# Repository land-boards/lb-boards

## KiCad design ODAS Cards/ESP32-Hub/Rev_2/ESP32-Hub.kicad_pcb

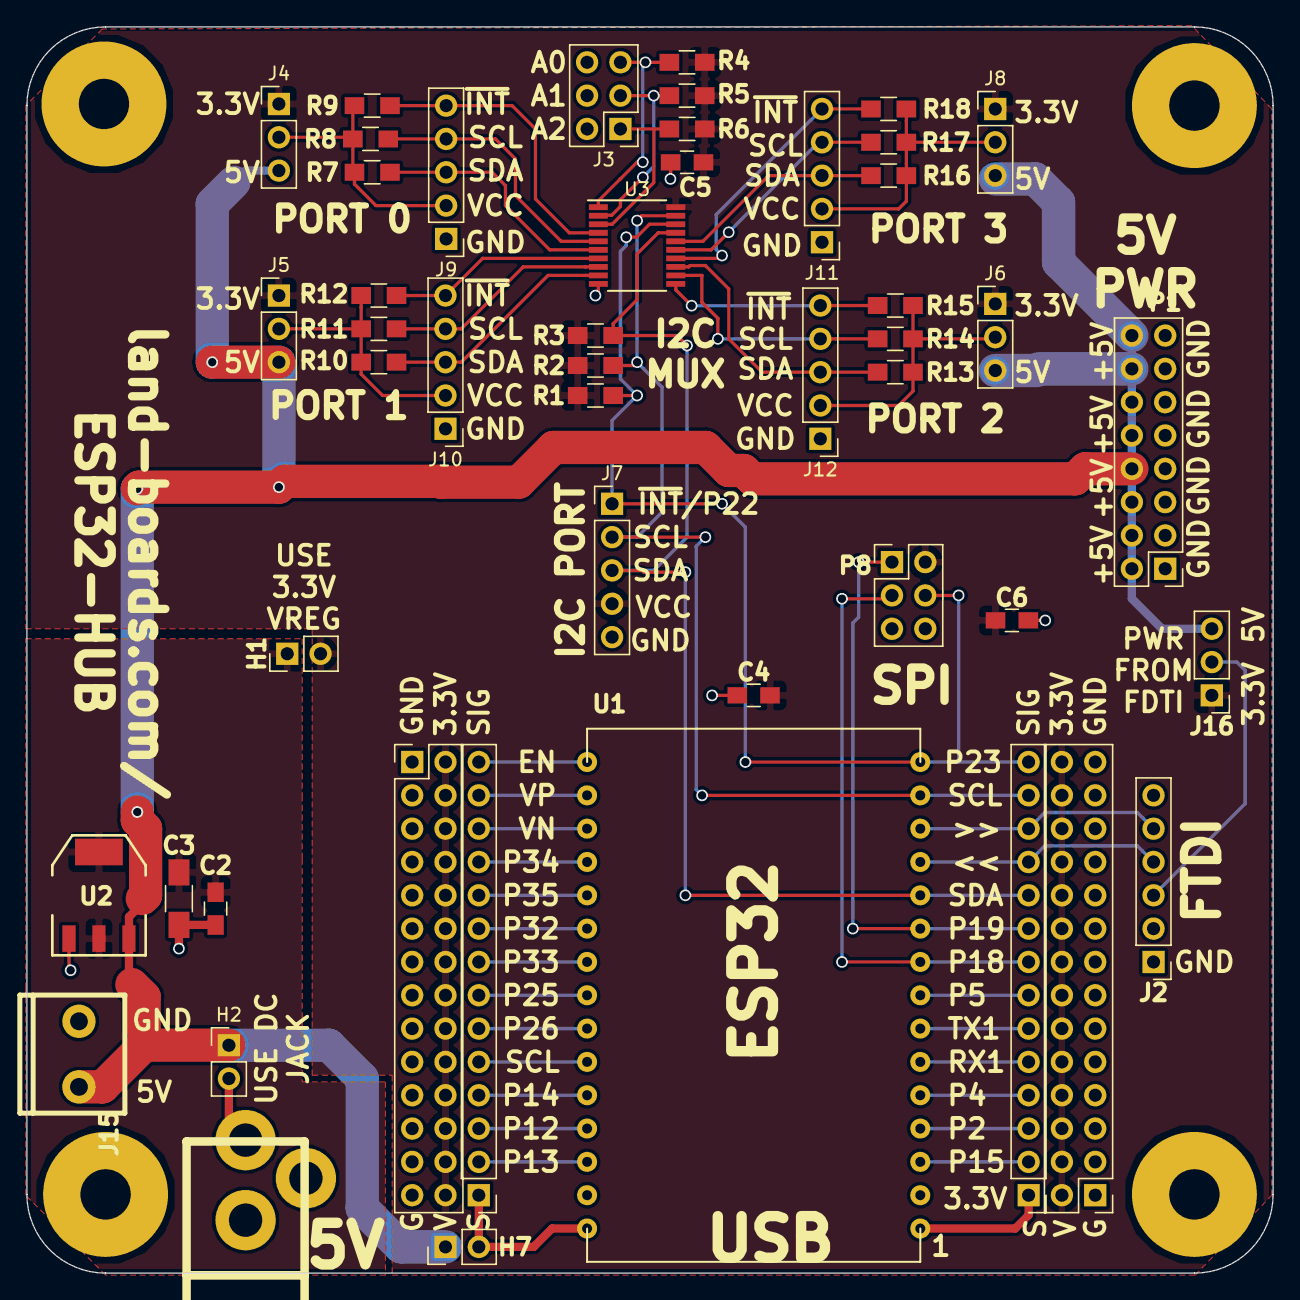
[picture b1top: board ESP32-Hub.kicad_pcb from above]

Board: 2 copper layers, 95.0 x 95.0 mm, 53 parts (0 on the bottom side), 53 nets.

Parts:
C2, C4, C5, C6: 0.1uF; C_0805_HandSoldering
C3: 10uF; C_1206_HandSoldering
H1, H2, H7: Conn_01x02; Pin_Header_Straight_1x02_Pitch2.54mm
J1: DCJ0202; DCJ-NEW
J2: FTDI; Pin_Header_Straight_1x06_Pitch2.54mm
J3: Conn_02x03_Odd_Even; Pin_Header_Straight_2x03_Pitch2.54mm
J4, J5, J6, J8, J16: Conn_01x03; Pin_Header_Straight_1x03_Pitch2.54mm
J7, J9, J10, J11, J12: Conn_01x05; Pin_Header_Straight_1x05_Pitch2.54mm
J15: Conn_01x02; TB2-5MM
MTG1, MTG2, MTG3: MTG_HOLE; MTG-6-32
MTG?1: MTG_HOLE; MTG-6-32
P1: Conn_02x08_Odd_Even; Pin_Header_Straight_2x08_Pitch2.54mm
P2, P11: Conn_02x14_Odd_Even; Pin_Header_Straight_2x14_Pitch2.54mm
P8: Conn_02x03_Odd_Even; Pin_Header_Straight_2x03_Pitch2.54mm
P12, P13: Conn_01x14; Pin_Header_Straight_1x14_Pitch2.54mm
R1, R4, R5, R6, R9, R12, R15, R18: 10K; R_0805_HandSoldering
R2, R3, R7, R8, R10, R11, R13, R14, R16, R17: 2.2K; R_0805_HandSoldering
U1: ESP32; ESP32_EXP
U2: AP1117; SOT223
U3: TCA9544A; TSSOP-20_4.4x6.5mm_Pitch0.65mm

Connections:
+3V3: C4.1, C5.1, C6.1, H1.2, J4.1, J5.1, J6.1, J7.4, J8.1, J16.1, P2.2, P2.4, P2.6, P2.8, P2.10, P2.12, P2.14, P2.16, P2.18, P2.20, P2.22, P2.24, P2.26, P2.28, P8.2, P11.2, P11.4, P11.6, P11.8, P11.10, P11.12, P11.14, P11.16, P11.18, P11.20, P11.22, P11.24, P11.26, P11.28, R1.1, R2.1, R3.1, R4.1, R5.1, R6.1, U3.20
+5V: H2.1, H7.1, J4.3, J5.3, J6.3, J8.3, J15.1, J16.3, P1.2, P1.4, P1.6, P1.8, P1.10, P1.12, P1.14, P1.16, U2.3
/A0: J3.5, R4.2, U3.1
/A1: J3.3, R5.2, U3.2
/A2: J3.1, R6.2, U3.3
/DCIN: H2.2, J1.1
/EN: P13.14, U1.16
/GP2: P12.3, U1.4
/GP4: P12.4, U1.5
/GP5: P12.7, U1.8
/GP12: P13.3, U1.27
/GP13: P13.2, U1.28
/GP14: P13.4, U1.26
/GP15: P12.2, U1.3
/GP18: P8.3, P12.8, U1.9
/GP19: P8.1, P12.9, U1.10
/GP23: J7.3, P8.4, P12.14, R3.2, U1.15, U3.17
/GP25: P13.7, U1.23
/GP26: P13.6, U1.24
/GP27: P13.5, U1.25
/GP32: P13.9, U1.21
/GP33: P13.8, U1.22
/GP34: P13.11, U1.19
/GP35: P13.10, U1.20
/INT0: J9.5, R9.2, U3.4
/INT1: J10.5, R12.2, U3.7
/INT2: J12.5, R15.2, U3.11
/INT3: J11.5, R18.2, U3.14
/RX0: J2.4, P12.11, U1.12
/RX1: P12.5, U1.6
/SC0: J9.4, R8.2, U3.5
/SC1: J10.4, R11.2, U3.8
/SC2: J12.4, R14.2, U3.12
/SC3: J11.4, R17.2, U3.15
/SD0: J9.3, R7.2, U3.6
/SD1: J10.3, R10.2, U3.9
/SD2: J12.3, R13.2, U3.13
/SD3: J11.3, R16.2, U3.16
/STM_SCL: J7.1, P12.13, R1.2, U1.14, U3.18
/STM_SDA: J7.2, P12.10, R2.2, U1.11, U3.19
/TX0: J2.5, P12.12, U1.13
/TX2: P12.6, U1.7
/VN: P13.12, U1.18
/VO3: C2.1, C3.1, H1.1, U2.2, U2.4
/VP: P13.13, U1.17
GND: C2.2, C3.2, C4.2, C5.2, C6.2, J1.2, J1.3, J2.1, J3.2, J3.4, J3.6, J7.5, J9.1, J10.1, J11.1, J12.1, J15.2, P1.1, P1.3, P1.5, P1.7, P1.9, P1.11, P1.13, P1.15, P2.1, P2.3, P2.5, P2.7, P2.9, P2.11, P2.13, P2.15, P2.17, P2.19, P2.21, P2.23, P2.25, P2.27, P8.6, P11.1, P11.3, P11.5, P11.7, P11.9, P11.11, P11.13, P11.15, P11.17, P11.19, P11.21, P11.23, P11.25, P11.27, U1.2, U1.29, U2.1, U3.10
unnamed: H7.2, P13.1, U1.30
unnamed: J4.2, J9.2, R7.1, R8.1, R9.1
unnamed: J5.2, J10.2, R10.1, R11.1, R12.1
unnamed: J8.2, J11.2, R16.1, R17.1, R18.1
unnamed: J6.2, J12.2, R13.1, R14.1, R15.1
unnamed: J2.3, J16.2
unnamed: P12.1, U1.1

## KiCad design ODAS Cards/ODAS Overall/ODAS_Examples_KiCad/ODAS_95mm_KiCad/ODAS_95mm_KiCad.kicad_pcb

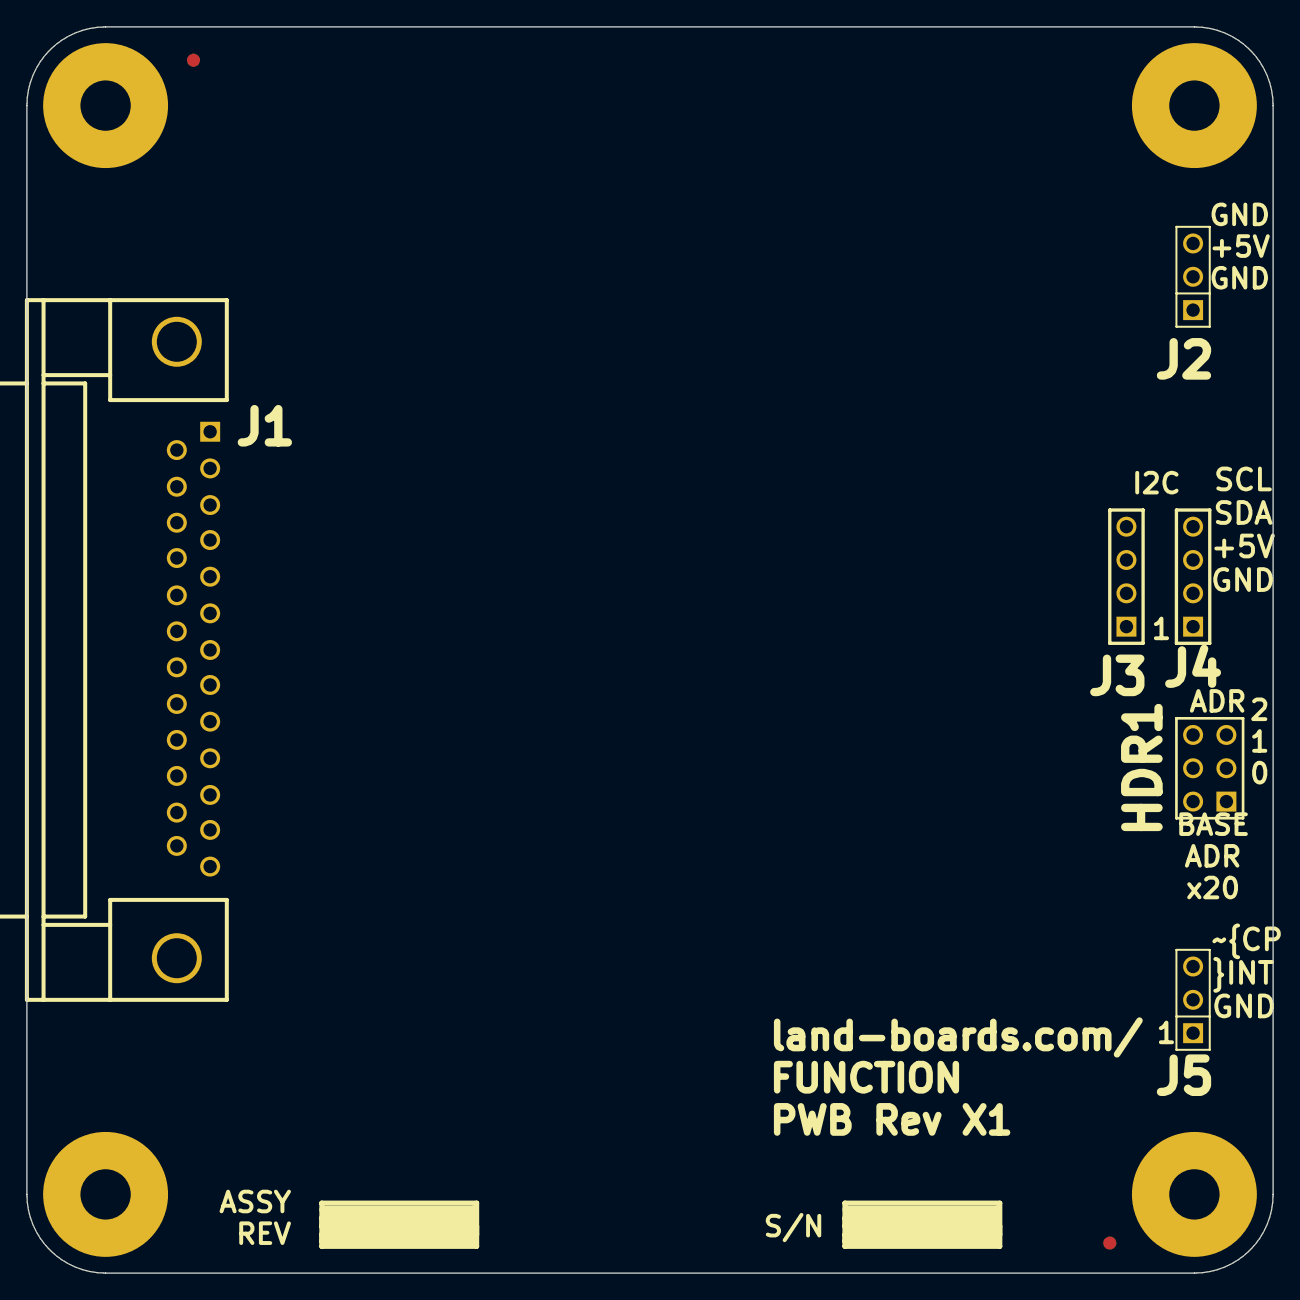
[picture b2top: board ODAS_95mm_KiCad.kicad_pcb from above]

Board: 2 copper layers, 95.0 x 95.0 mm, 14 parts (0 on the bottom side), 4 nets.

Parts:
FID1, FID2: ADAFRUIT_FIDUCIAL; FIDUCIAL
HDR1: CONN_3X2; pin_array_3x2
J1: DB25; DB25MC
J2, J5: CONN_3; PIN_ARRAY_3X1
J3, J4: CONN_4; PIN_ARRAY_4x1
MTG1, MTG2, MTG3, MTG4: MTG_HOLE; MTG-6-32
ST1: CONN_1; REV_BLOCK
ST2: REV-HIST; REV_BLOCK

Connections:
/GND: HDR1.1, HDR1.3, HDR1.5, J2.1, J2.3, J3.1, J4.1, J5.1, J5.3
/SCK: J3.4, J4.4
/SDA: J3.3, J4.3
/VCC: J2.2, J3.2, J4.2

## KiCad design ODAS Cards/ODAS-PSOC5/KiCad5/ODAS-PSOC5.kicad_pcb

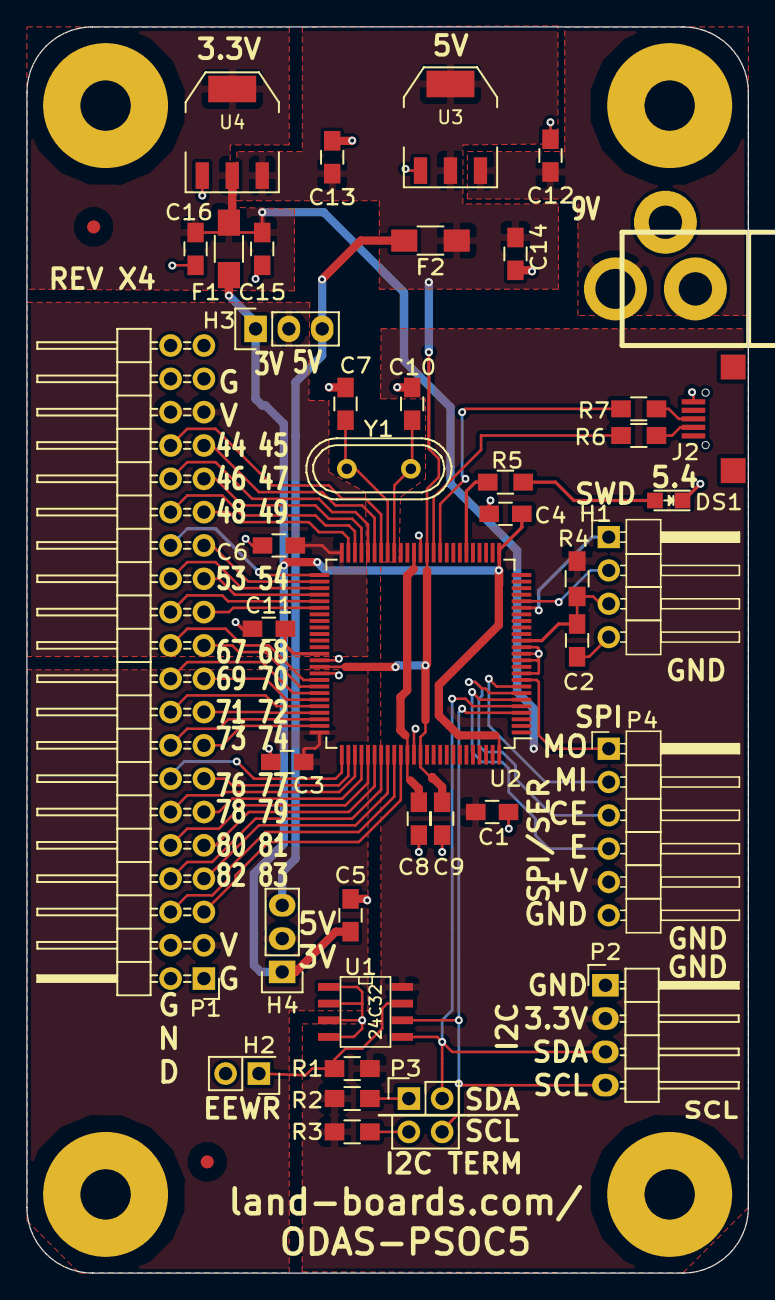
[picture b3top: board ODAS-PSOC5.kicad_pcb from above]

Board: 2 copper layers, 55.0 x 95.0 mm, 48 parts (1 on the bottom side), 60 nets.

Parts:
C1, C2, C3, C4, C5, C6, C9, C12, C13, C14, C15, C16: 0.1uF; C_0805_HandSoldering
C7, C10: C; C_0805_HandSoldering
C8, C11: 1uF; C_0805_HandSoldering
DS1: LED-fixed; LED_0805
F1, F2: FUSE; R_1206_HandSoldering
FID1, FID2: CONN_1; FIDUCIAL
H1: CONN_01X04; Pin_Header_Angled_1x04_Pitch2.54mm
H2: CONN_2; Pin_Header_Straight_2x01
H3, H4: CONN_01X03; Pin_Header_Straight_1x03
J1: DCJ0202; JACK_3.5MM
J2: USB-MICRO-B; USB_Micro-B-Wellco-SMT
MTG1, MTG2, MTG3, MTG4: CONN_1; MTG-6-32
P1: CONN_01X40; Pin_Header_Angled_2x20
P2: CONN_01X04; Pin_Header_Angled_1x04
P3: CONN_02X02; Pin_Header_Straight_2x02
P4: CONN_01X06; Pin_Header_Angled_1x06_Pitch2.54mm
R1: 1K; R_0805_HandSoldering
R2, R3, R4: 3.9K; R_0805_HandSoldering
R5: 120; R_0805_HandSoldering
R6, R7: 22; R_0805_HandSoldering
TEST: COUPON; REV_BLOCK
U1: 24C32; SO8E-wider
U2: CY8C5267AXI-LP051; TQFP-100_14x14mm_Pitch0.5mm
U3, U4: AP1117; SOT-223
Y1: Crystal_Small; Crystal_HC49-U_Vertical

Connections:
+3.3VP: C4.1, C5.1, F1.1, H3.1, H4.1, U2.26, U2.100
+3V3: C1.1, C15.1, C16.1, F1.2, P2.2, P4.5, R1.1, R2.2, R3.2, R4.2, U1.8, U4.2, U4.4
+5V: C9.2, C13.1, C14.1, F2.2, U2.37, U2.65, U2.88, U3.2, U3.4, U4.3
+5VP: F2.1, H3.3, H4.3
/+9V: C12.1, J1.1, U3.3
/IO_22: C2.1, H1.3, R4.1, U2.15
/IO_23: H1.2, U2.21
/IO_24: H1.1, U2.20
/P5-4: R5.1, U2.31
/P44: P1.34, U2.44
/P45: P1.33, U2.45
/P46: P1.32, U2.46
/P47: P1.31, U2.47
/P48: P1.30, U2.48
/P49: P1.29, U2.49
/P51: P1.28, U2.51
/P52: P1.27, U2.52
/P53: P1.26, U2.53
/P54: P1.25, U2.54
/P55: P1.24, U2.55
/P56: P1.23, U2.56
/P67: P1.22, U2.67
/P68: P1.21, U2.68
/P69: P1.20, U2.69
/P70: P1.19, U2.70
/P71: P1.18, U2.71
/P72: P1.17, U2.72
/P73: P1.16, U2.73
/P74: P1.15, U2.74
/P76: P1.14, U2.76
/P77: P1.13, U2.77
/P78: P1.12, U2.78
/P79: P1.11, U2.79
/P80: P1.10, U2.80
/P81: P1.9, U2.81
/P82: P1.8, U2.82
/P83: P1.7, U2.83
/P84: P1.6, U2.84
/P85: P1.5, U2.85
/SCL: P2.4, P3.4, U1.6, U2.4
/SDA: P2.3, P3.2, U1.5, U2.5
/SPICE0: P4.4, U2.6
/SPIMISO: P4.2, U2.8
/SPIMOSI: P4.1, U2.9
/SPISCK: P4.3, U2.7
/USB-DM: J2.2, R6.1
/USB-DP: J2.3, R7.1
/VZ0: C3.1, H4.2, P1.3, P1.4, U2.75
/VZ3: C6.1, H3.2, P1.35, P1.36, U2.50
/WR: H2.1, R1.2, U1.7
GND: C1.2, C2.2, C3.2, C4.2, C5.2, C6.2, C7.1, C8.1, C9.1, C10.1, C11.1, C12.2, C13.2, C14.2, C15.2, C16.2, DS1.1, H1.4, H2.2, J1.2, J1.3, J2.5, P1.1, P1.2, P1.37, P1.38, P2.1, P4.6, U1.1, U1.2, U1.3, U1.4, U2.10, U2.12, U2.13, U2.14, U2.38, U2.64, U2.66, U2.87, U3.1, U4.1
unnamed: C7.2, U2.43, Y1.1
unnamed: C8.2, U2.39, U2.86
unnamed: C10.2, U2.42, Y1.2
unnamed: C11.2, U2.63
unnamed: DS1.2, R5.2
unnamed: P3.1, R2.1
unnamed: P3.3, R3.1
unnamed: R6.2, U2.36
unnamed: R7.2, U2.35
